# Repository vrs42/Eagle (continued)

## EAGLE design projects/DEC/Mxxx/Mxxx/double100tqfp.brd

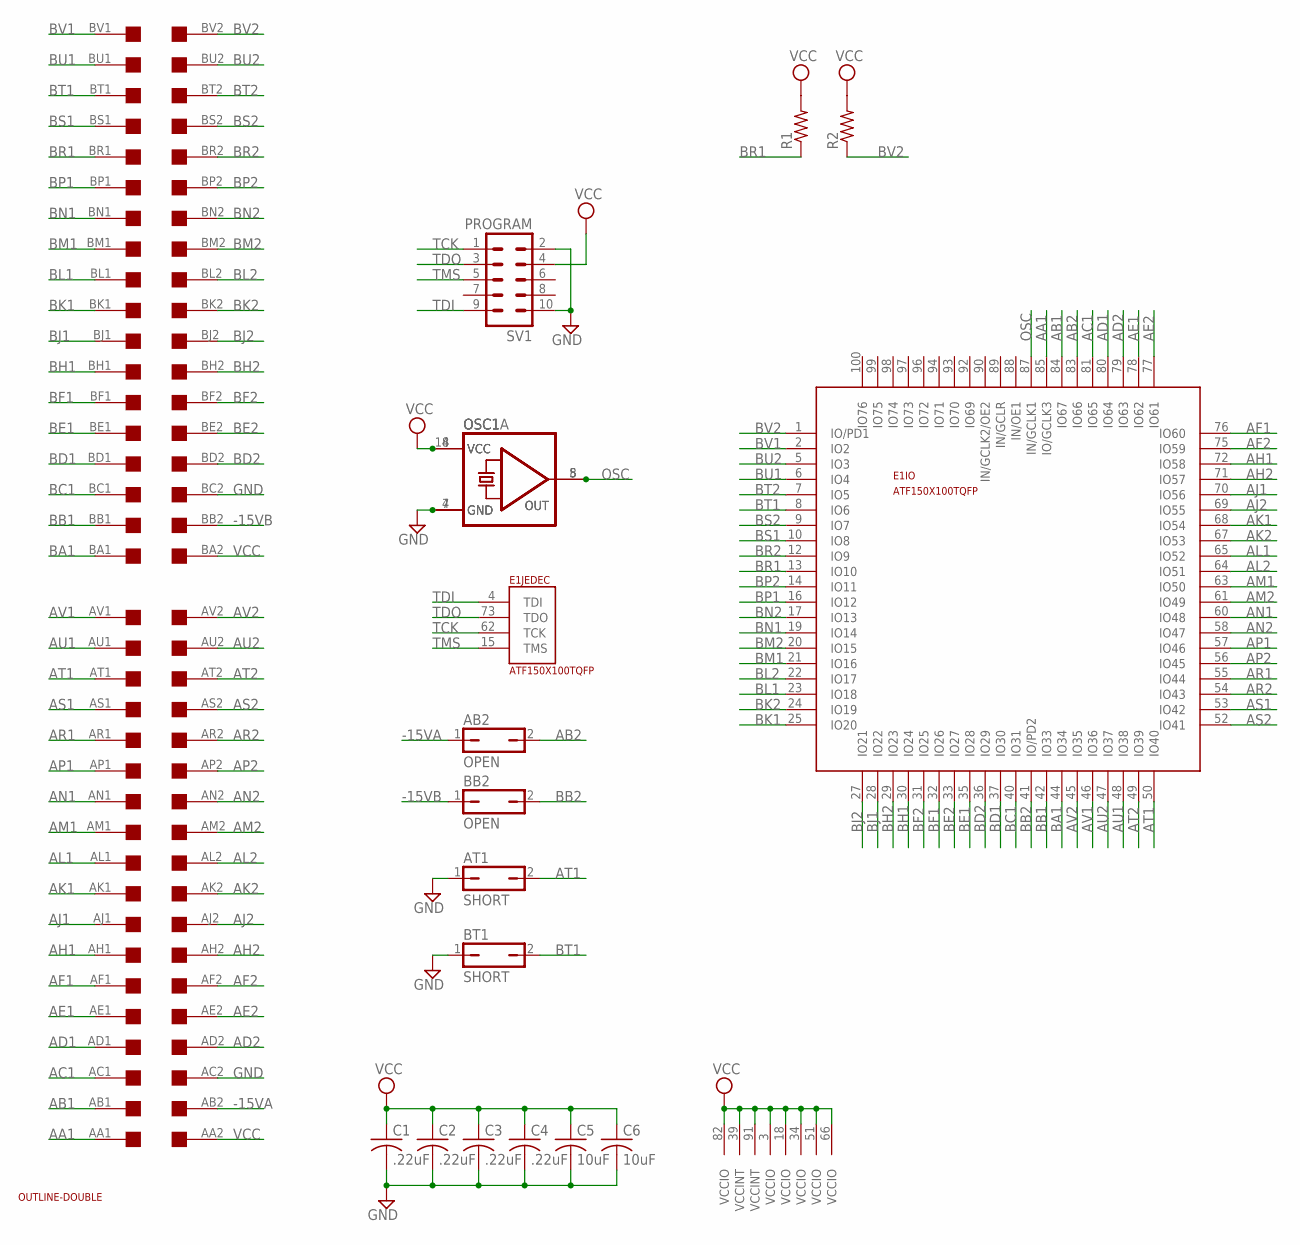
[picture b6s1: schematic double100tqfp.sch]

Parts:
AB2: OPEN; JP1
AT1: SHORT; JP1
BB2: OPEN; JP1
BT1: SHORT; JP1
C1, C2, C3, C4: .22uF; C0805
C5, C6: 10uF; C0805
E1: ATF150X100TQFP; TQFP-100
OSC1: DIL08S
OSC1A: DIL14S
R1, R2: 0207/10
SV1: PROGRAM; ML10
U$1: DOUBLE; EDGE-CON4
U$3: OUTLINE-DOUBLE; DOUBLE

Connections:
-15VA: AB2.1, U$1.AB2
-15VB: BB2.1, U$1.BB2
AA1: E1.85 (IO/GCLK3), U$1.AA1
AB1: E1.84 (IO67), U$1.AB1
AB2: AB2.2, E1.83 (IO66)
AC1: E1.81 (IO65), U$1.AC1
AD1: E1.80 (IO64), U$1.AD1
AD2: E1.79 (IO63), U$1.AD2
AE1: E1.78 (IO62), U$1.AE1
AE2: E1.77 (IO61), U$1.AE2
AF1: E1.76 (IO60), U$1.AF1
AF2: E1.75 (IO59), U$1.AF2
AH1: E1.72 (IO58), U$1.AH1
AH2: E1.71 (IO57), U$1.AH2
AJ1: E1.70 (IO56), U$1.AJ1
AJ2: E1.69 (IO55), U$1.AJ2
AK1: E1.68 (IO54), U$1.AK1
AK2: E1.67 (IO53), U$1.AK2
AL1: E1.65 (IO52), U$1.AL1
AL2: E1.64 (IO51), U$1.AL2
AM1: E1.63 (IO50), U$1.AM1
AM2: E1.61 (IO49), U$1.AM2
AN1: E1.60 (IO48), U$1.AN1
AN2: E1.58 (IO47), U$1.AN2
AP1: E1.57 (IO46), U$1.AP1
AP2: E1.56 (IO45), U$1.AP2
AR1: E1.55 (IO44), U$1.AR1
AR2: E1.54 (IO43), U$1.AR2
AS1: E1.53 (IO42), U$1.AS1
AS2: E1.52 (IO41), U$1.AS2
AT1: AT1.2, E1.50 (IO40), U$1.AT1
AT2: E1.49 (IO39), U$1.AT2
AU1: E1.48 (IO38), U$1.AU1
AU2: E1.47 (IO37), U$1.AU2
AV1: E1.46 (IO36), U$1.AV1
AV2: E1.45 (IO35), U$1.AV2
BA1: E1.44 (IO34), U$1.BA1
BB1: E1.42 (IO33), U$1.BB1
BB2: BB2.2, E1.41 (IO/PD2)
BC1: E1.40 (IO31), U$1.BC1
BD1: E1.37 (IO30), U$1.BD1
BD2: E1.36 (IO29), U$1.BD2
BE1: E1.35 (IO28), U$1.BE1
BE2: E1.33 (IO27), U$1.BE2
BF1: E1.32 (IO26), U$1.BF1
BF2: E1.31 (IO25), U$1.BF2
BH1: E1.30 (IO24), U$1.BH1
BH2: E1.29 (IO23), U$1.BH2
BJ1: E1.28 (IO22), U$1.BJ1
BJ2: E1.27 (IO21), U$1.BJ2
BK1: E1.25 (IO20), U$1.BK1
BK2: E1.24 (IO19), U$1.BK2
BL1: E1.23 (IO18), U$1.BL1
BL2: E1.22 (IO17), U$1.BL2
BM1: E1.21 (IO16), U$1.BM1
BM2: E1.20 (IO15), U$1.BM2
BN1: E1.19 (IO14), U$1.BN1
BN2: E1.17 (IO13), U$1.BN2
BP1: E1.16 (IO12), U$1.BP1
BP2: E1.14 (IO11), U$1.BP2
BR1: E1.13 (IO10), R1.1, U$1.BR1
BR2: E1.12 (IO9), U$1.BR2
BS1: E1.10 (IO8), U$1.BS1
BS2: E1.9 (IO7), U$1.BS2
BT1: BT1.2, E1.8 (IO6), U$1.BT1
BT2: E1.7 (IO5), U$1.BT2
BU1: E1.6 (IO4), U$1.BU1
BU2: E1.5 (IO3), U$1.BU2
BV1: E1.2 (IO2), U$1.BV1
BV2: E1.1 (IO/PD1), R2.1, U$1.BV2
GND: AT1.1, BT1.1, C1.2, C2.2, C3.2, C4.2, C5.2, C6.2, E1.11 (GND), E1.26 (GND), E1.38 (GND), E1.43 (GND), E1.59 (GND), E1.74 (GND), E1.86 (GND), E1.95 (GND), OSC1.4 (GND), OSC1A.7 (GND), SV1.2, SV1.10, U$1.AC2, U$1.BC2
OSC: E1.87 (IN/GCLK1), OSC1.5 (OUT), OSC1A.8 (OUT)
TCK: E1.62 (TCK), SV1.1
TDI: E1.4 (TDI), SV1.9
TDO: E1.73 (TDO), SV1.3
TMS: E1.15 (TMS), SV1.5
VCC: C1.1, C2.1, C3.1, C4.1, C5.1, C6.1, E1.3 (VCCIO), E1.18 (VCCIO), E1.34 (VCCIO), E1.39 (VCCINT), E1.51 (VCCIO), E1.66 (VCCIO), E1.82 (VCCIO), E1.91 (VCCINT), OSC1.8 (VCC), OSC1A.14 (VCC), R1.2, R2.2, SV1.4, U$1.AA2, U$1.BA2

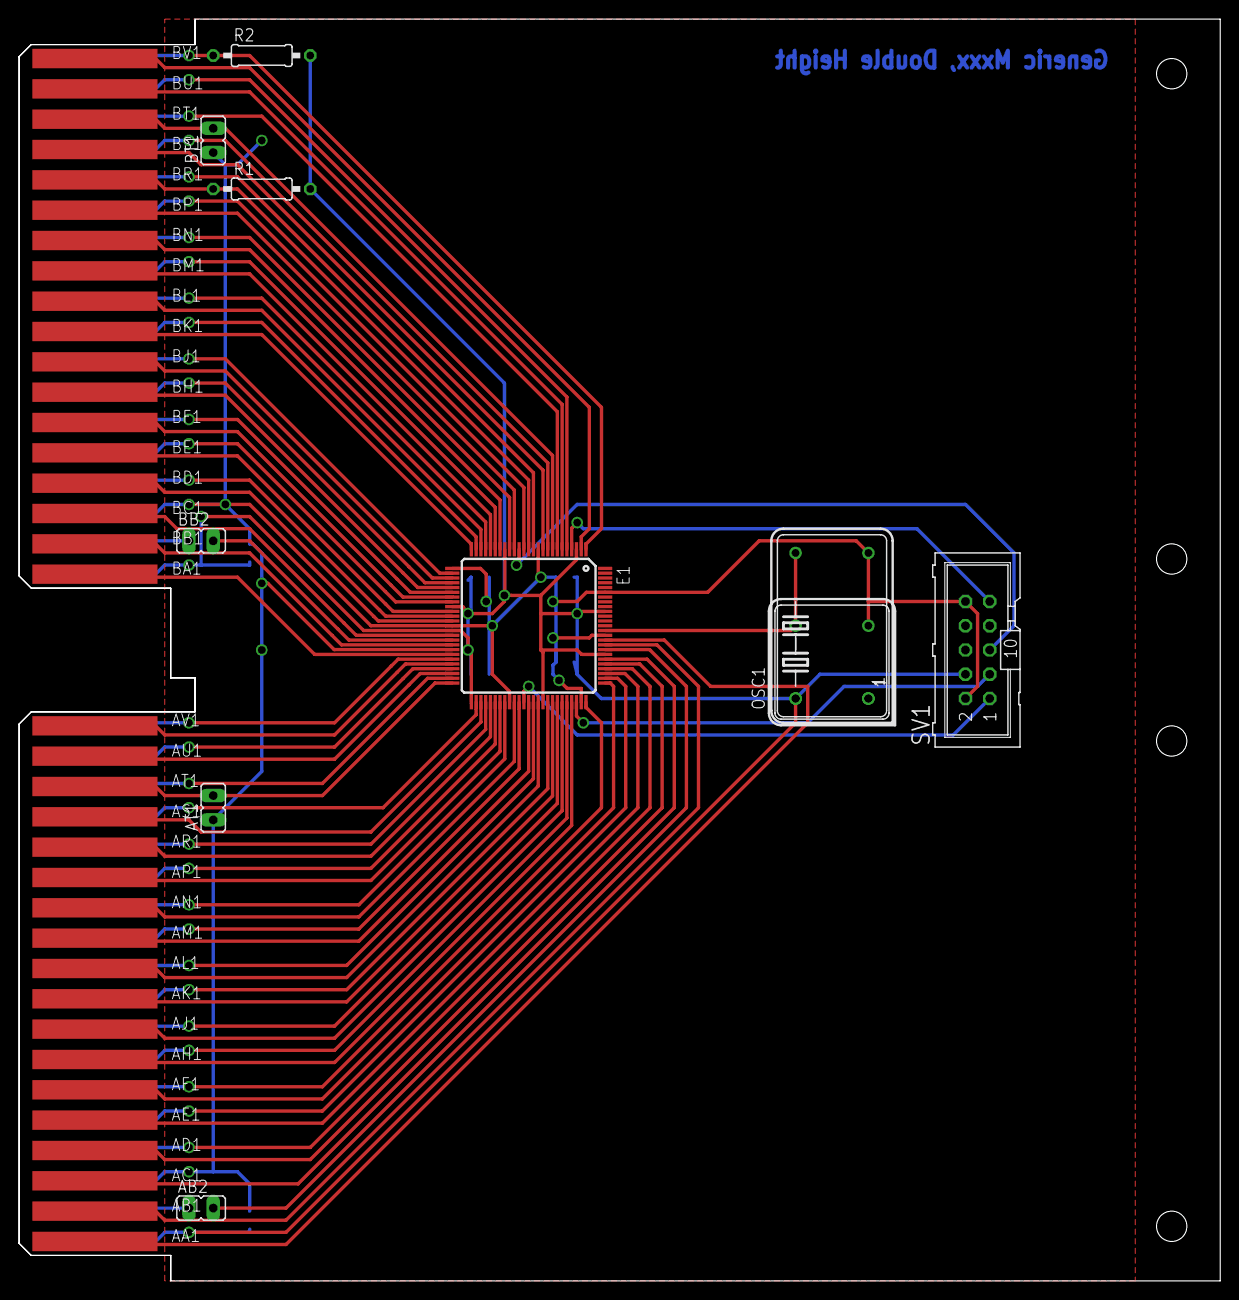
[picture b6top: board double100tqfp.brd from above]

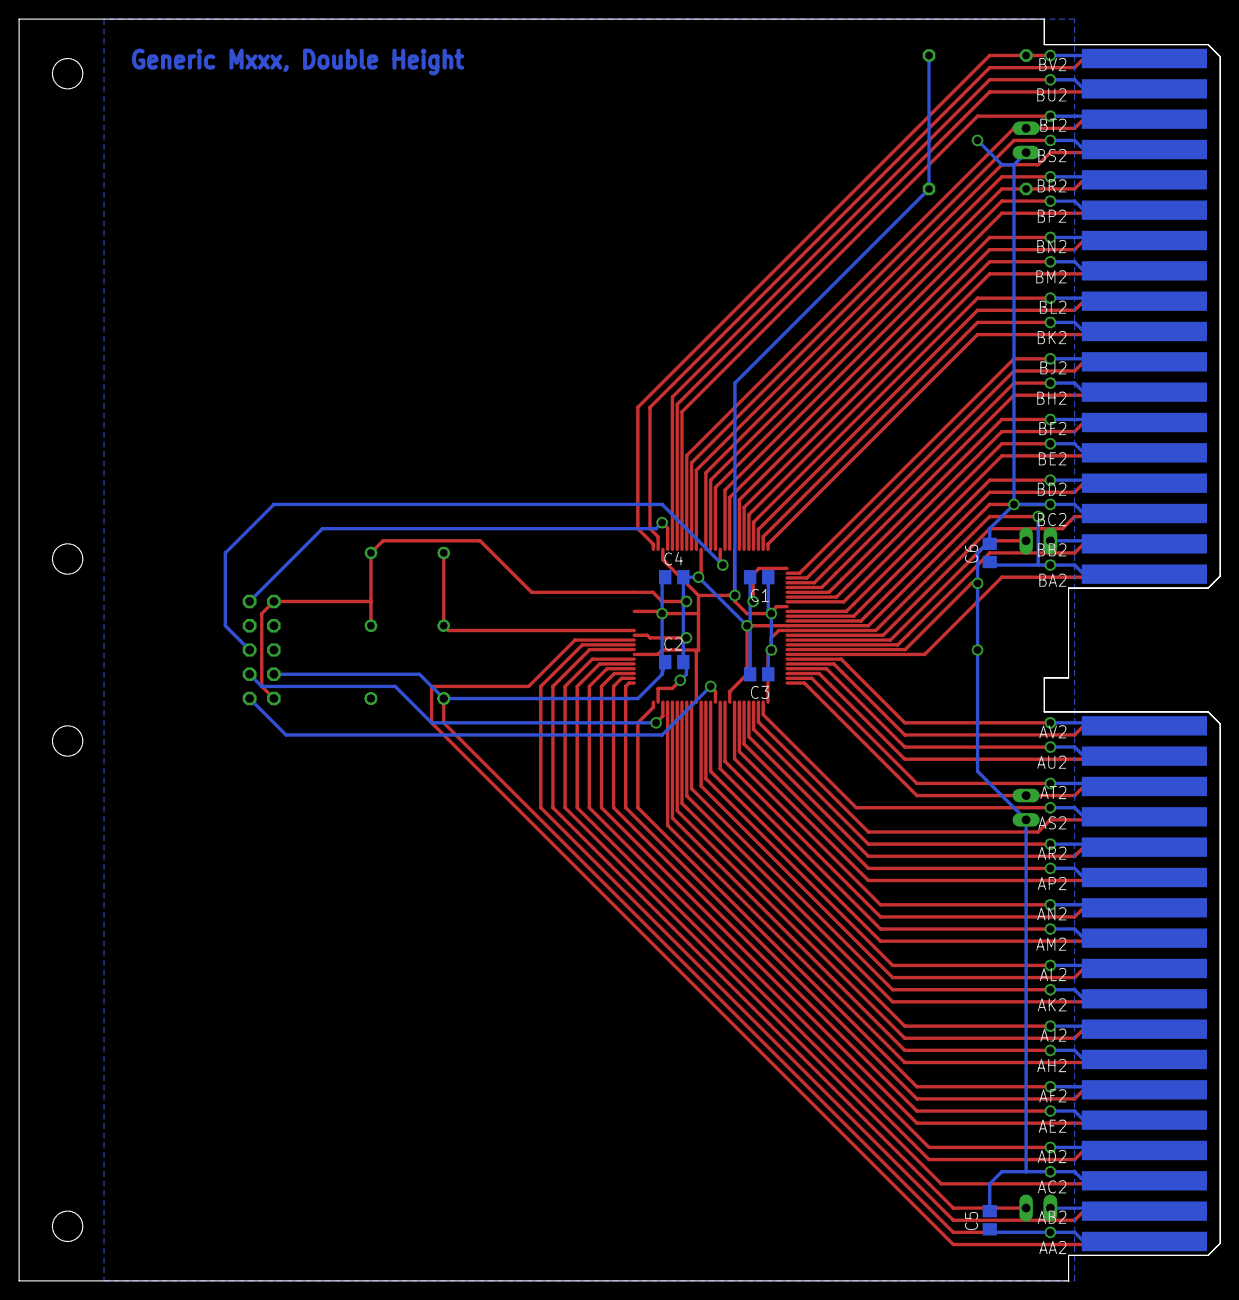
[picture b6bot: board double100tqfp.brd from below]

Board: 2 copper layers, 125.7 x 132.1 mm, 18 parts (6 on the bottom side), 77 nets.

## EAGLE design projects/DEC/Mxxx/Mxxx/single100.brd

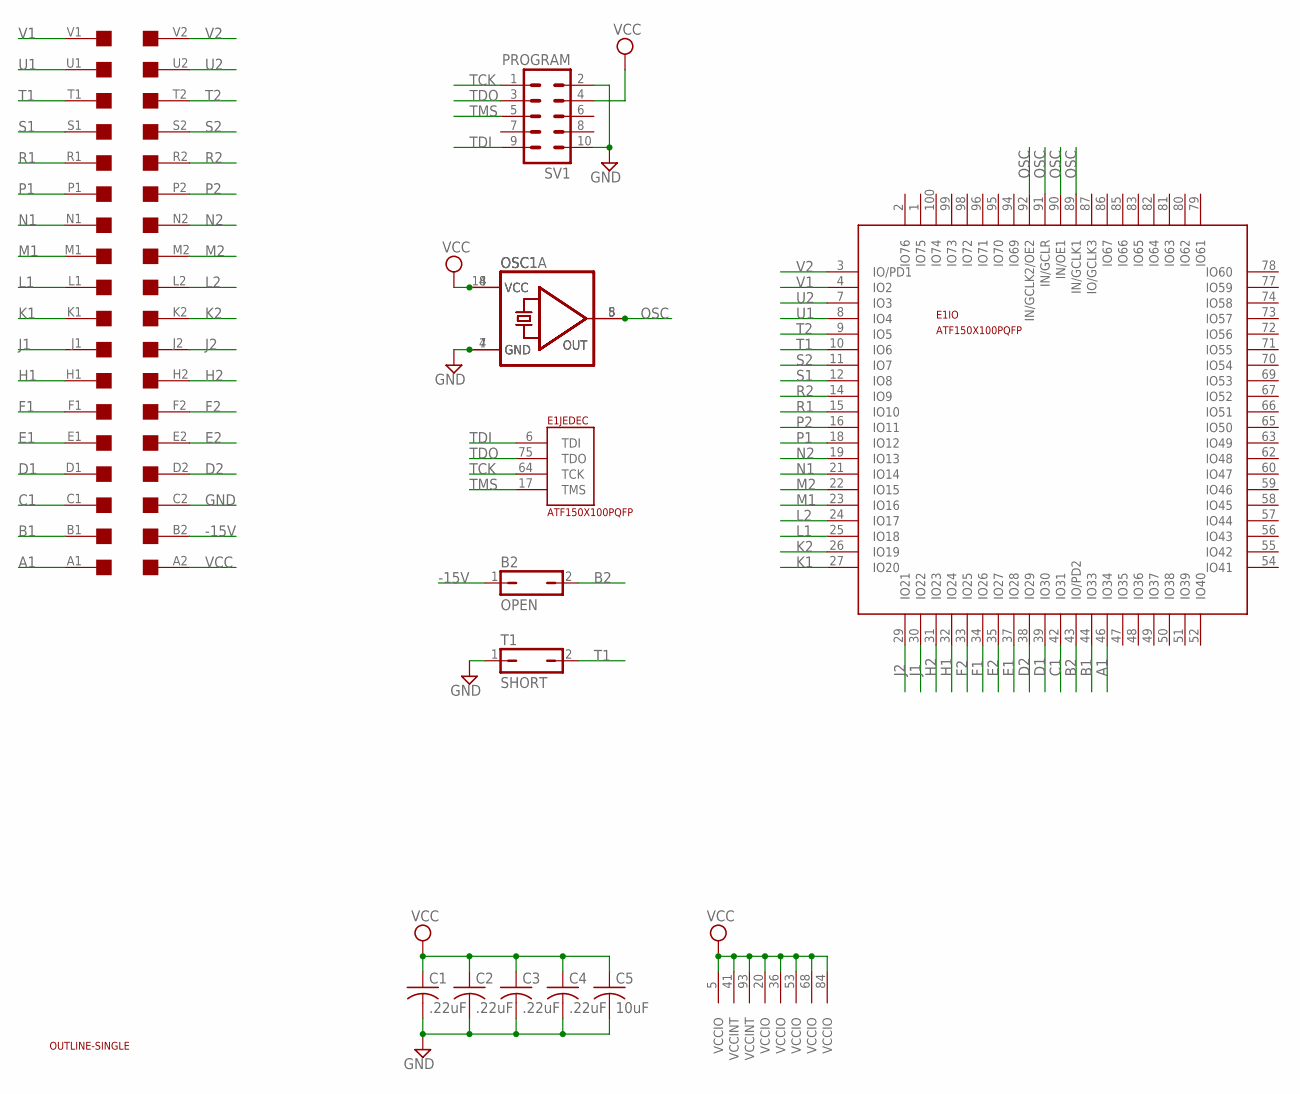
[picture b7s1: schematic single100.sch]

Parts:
B2: OPEN; JP1
C1, C2, C3, C4: .22uF; C0805
C5: 10uF; C0805
E1: ATF150X100PQFP; PQFP-100
OSC1: DIL08S
OSC1A: DIL14S
SV1: PROGRAM; ML10
T1: SHORT; JP1
U$1: OUTLINE-SINGLE; SINGLE
U$2: SINGLE; EDGE-CON2

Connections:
-15V: B2.1, U$2.B2
A1: E1.46 (IO34), U$2.A1
B1: E1.44 (IO33), U$2.B1
B2: B2.2, E1.43 (IO/PD2)
C1: E1.42 (IO31), U$2.C1
D1: E1.39 (IO30), U$2.D1
D2: E1.38 (IO29), U$2.D2
E1: E1.37 (IO28), U$2.E1
E2: E1.35 (IO27), U$2.E2
F1: E1.34 (IO26), U$2.F1
F2: E1.33 (IO25), U$2.F2
GND: C1.2, C2.2, C3.2, C4.2, C5.2, E1.13 (GND), E1.28 (GND), E1.40 (GND), E1.45 (GND), E1.61 (GND), E1.76 (GND), E1.88 (GND), E1.97 (GND), OSC1.4 (GND), OSC1A.7 (GND), SV1.2, SV1.10, T1.1, U$2.C2
H1: E1.32 (IO24), U$2.H1
H2: E1.31 (IO23), U$2.H2
J1: E1.30 (IO22), U$2.J1
J2: E1.29 (IO21), U$2.J2
K1: E1.27 (IO20), U$2.K1
K2: E1.26 (IO19), U$2.K2
L1: E1.25 (IO18), U$2.L1
L2: E1.24 (IO17), U$2.L2
M1: E1.23 (IO16), U$2.M1
M2: E1.22 (IO15), U$2.M2
N1: E1.21 (IO14), U$2.N1
N2: E1.19 (IO13), U$2.N2
OSC: E1.89 (IN/GCLK1), E1.90 (IN/OE1), E1.91 (IN/GCLR), E1.92 (IN/GCLK2/OE2), OSC1.5 (OUT), OSC1A.8 (OUT)
P1: E1.18 (IO12), U$2.P1
P2: E1.16 (IO11), U$2.P2
R1: E1.15 (IO10), U$2.R1
R2: E1.14 (IO9), U$2.R2
S1: E1.12 (IO8), U$2.S1
S2: E1.11 (IO7), U$2.S2
T1: E1.10 (IO6), T1.2, U$2.T1
T2: E1.9 (IO5), U$2.T2
TCK: E1.64 (TCK), SV1.1
TDI: E1.6 (TDI), SV1.9
TDO: E1.75 (TDO), SV1.3
TMS: E1.17 (TMS), SV1.5
U1: E1.8 (IO4), U$2.U1
U2: E1.7 (IO3), U$2.U2
V1: E1.4 (IO2), U$2.V1
V2: E1.3 (IO/PD1), U$2.V2
VCC: C1.1, C2.1, C3.1, C4.1, C5.1, E1.5 (VCCIO), E1.20 (VCCIO), E1.36 (VCCIO), E1.41 (VCCINT), E1.53 (VCCIO), E1.68 (VCCIO), E1.84 (VCCIO), E1.93 (VCCINT), OSC1.8 (VCC), OSC1A.14 (VCC), SV1.4, U$2.A2

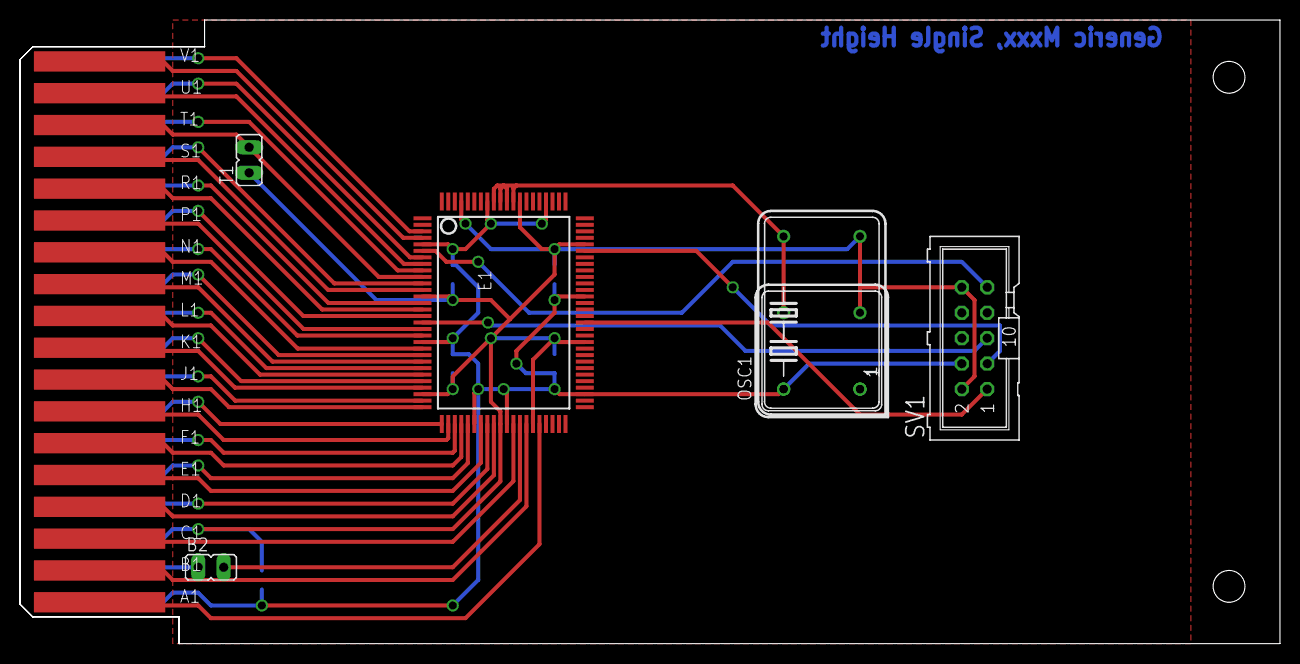
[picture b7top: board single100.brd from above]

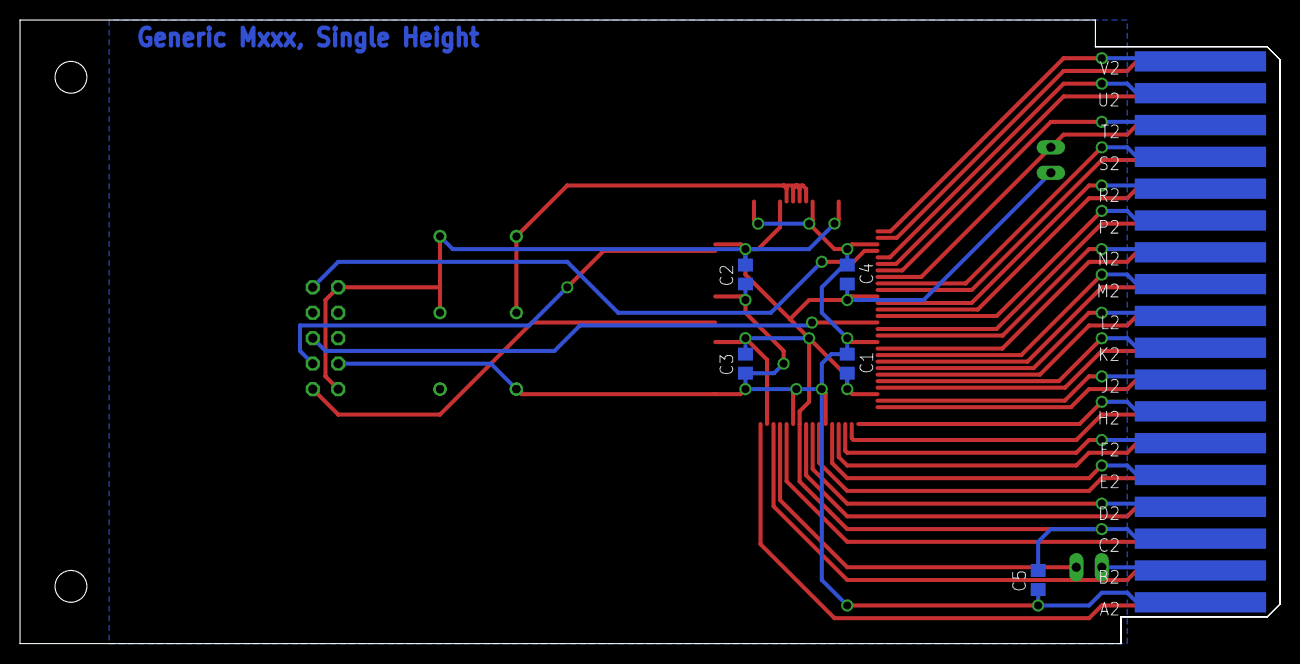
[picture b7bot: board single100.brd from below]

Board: 2 copper layers, 125.7 x 62.2 mm, 13 parts (5 on the bottom side), 42 nets.

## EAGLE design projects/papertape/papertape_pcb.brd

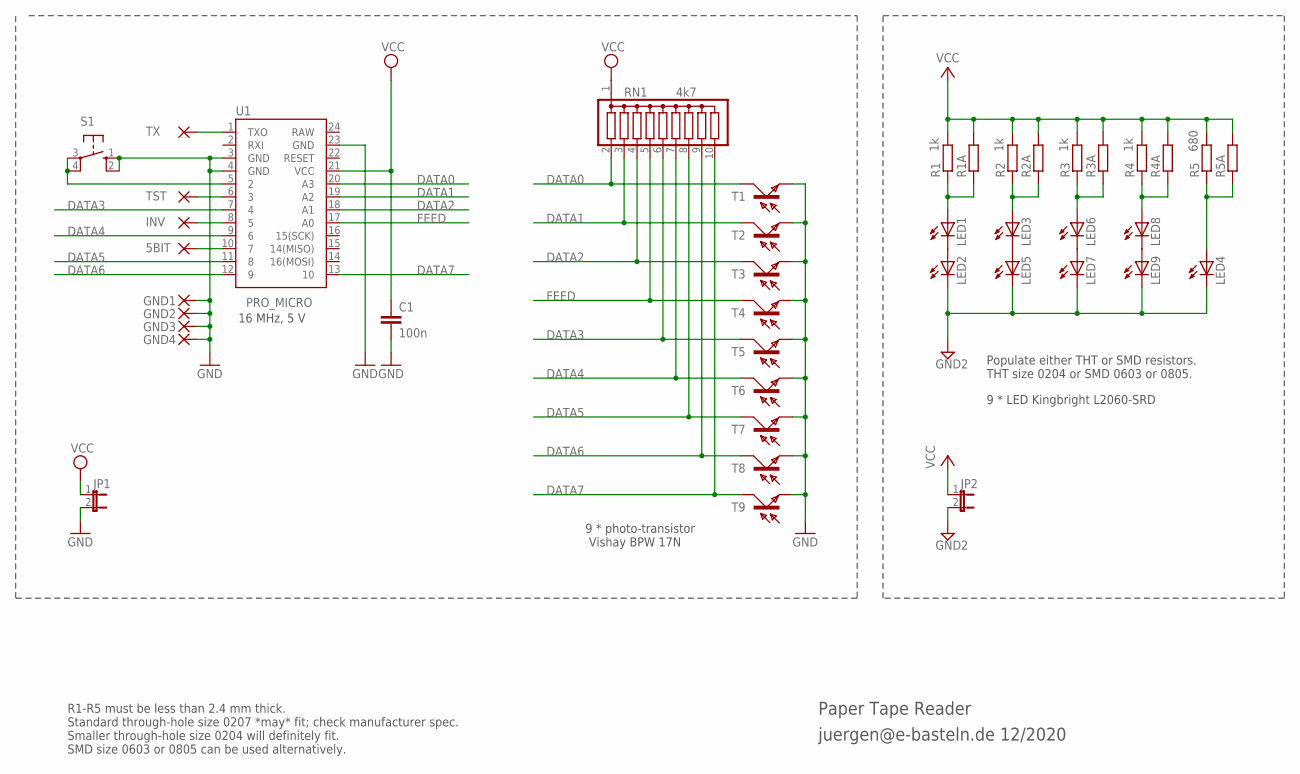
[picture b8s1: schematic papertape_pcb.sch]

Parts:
5BIT: 1,6/0,8
C1: 100n; C025-024X044
GND1, GND2, GND3, GND4: 1,6/0,8
INV: 1,6/0,8
JP1, JP2: JP1E; JP1
LED1, LED2, LED3, LED4, LED5, LED6, LED7, LED8, LED9: LEDLED1MM8; LED1MM8
R1, R2, R3, R4: 1k; 0204/7
R1A, R2A, R3A, R4A, R5A: R-EU_R0805; R0805
R5: 680; 0204/7
RN1: 4k7; SIL10
S1: 10-XX; B3F-10XX
T1, T2, T3, T4, T5, T6, T7, T8, T9: BPW17N
TST: 1,6/0,8
TX: 1,6/0,8
U1: PRO_MICRO; SPARKFUN_PRO_MICRO

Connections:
DATA0: RN1.2, T1.C, U1.20 (A3)
DATA1: RN1.3, T2.C, U1.19 (A2)
DATA2: RN1.4, T3.C, U1.18 (A1)
DATA3: RN1.6, T5.C, U1.7 (4)
DATA4: RN1.7, T6.C, U1.9 (6)
DATA5: RN1.8, T7.C, U1.11 (8)
DATA6: RN1.9, T8.C, U1.12 (9)
DATA7: RN1.10, T9.C, U1.13 (10)
FEED: RN1.5, T4.C, U1.17 (A0)
GND: C1.2, GND1.1, GND2.1, GND3.1, GND4.1, JP1.2, S1.1 (S), S1.2 (S1), T1.E, T2.E, T3.E, T4.E, T5.E, T6.E, T7.E, T8.E, T9.E, U1.3 (GND), U1.4 (GND), U1.23 (GND)
GND2: JP2.2, LED2.K (C), LED4.K (C), LED5.K (C), LED7.K (C), LED9.K (C)
unnamed: LED1.K (C), LED2.A
unnamed: LED3.K (C), LED5.A
unnamed: LED6.K (C), LED7.A
unnamed: LED8.K (C), LED9.A
unnamed: INV.1, U1.8 (5)
unnamed: TST.1, U1.6 (3)
unnamed: LED4.A, R5.1, R5A.1
unnamed: TX.1, U1.1 (TXO)
unnamed: 5BIT.1, U1.10 (7)
unnamed: S1.3, S1.4 (P1), U1.5 (2)
unnamed: LED1.A, R1.1, R1A.1
unnamed: LED3.A, R2.1, R2A.1
unnamed: LED6.A, R3.1, R3A.1
unnamed: LED8.A, R4.1, R4A.1
RAW: U1.24 (RAW)
VCC: C1.1, JP1.1, RN1.1, U1.21 (VCC)
VCC2: JP2.1, R1.2, R1A.2, R2.2, R2A.2, R3.2, R3A.2, R4.2, R4A.2, R5.2, R5A.2

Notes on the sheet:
16 MHz, 5 V
9 * photo-transistor Vishay BPW 17N
9 * LED Kingbright L2060-SRD
R1-R5 must be less than 2.4 mm thick. Standard through-hole size 0207 *may* fit; check manufacturer spec. Smaller through-hole size 0204 will definitely fit. SMD size 0603 or 0805 can be used alternatively.
Paper Tape Reader
juergen@e-basteln.de 12/2020
Populate either THT or SMD resistors. THT size 0204 or SMD 0603 or 0805.

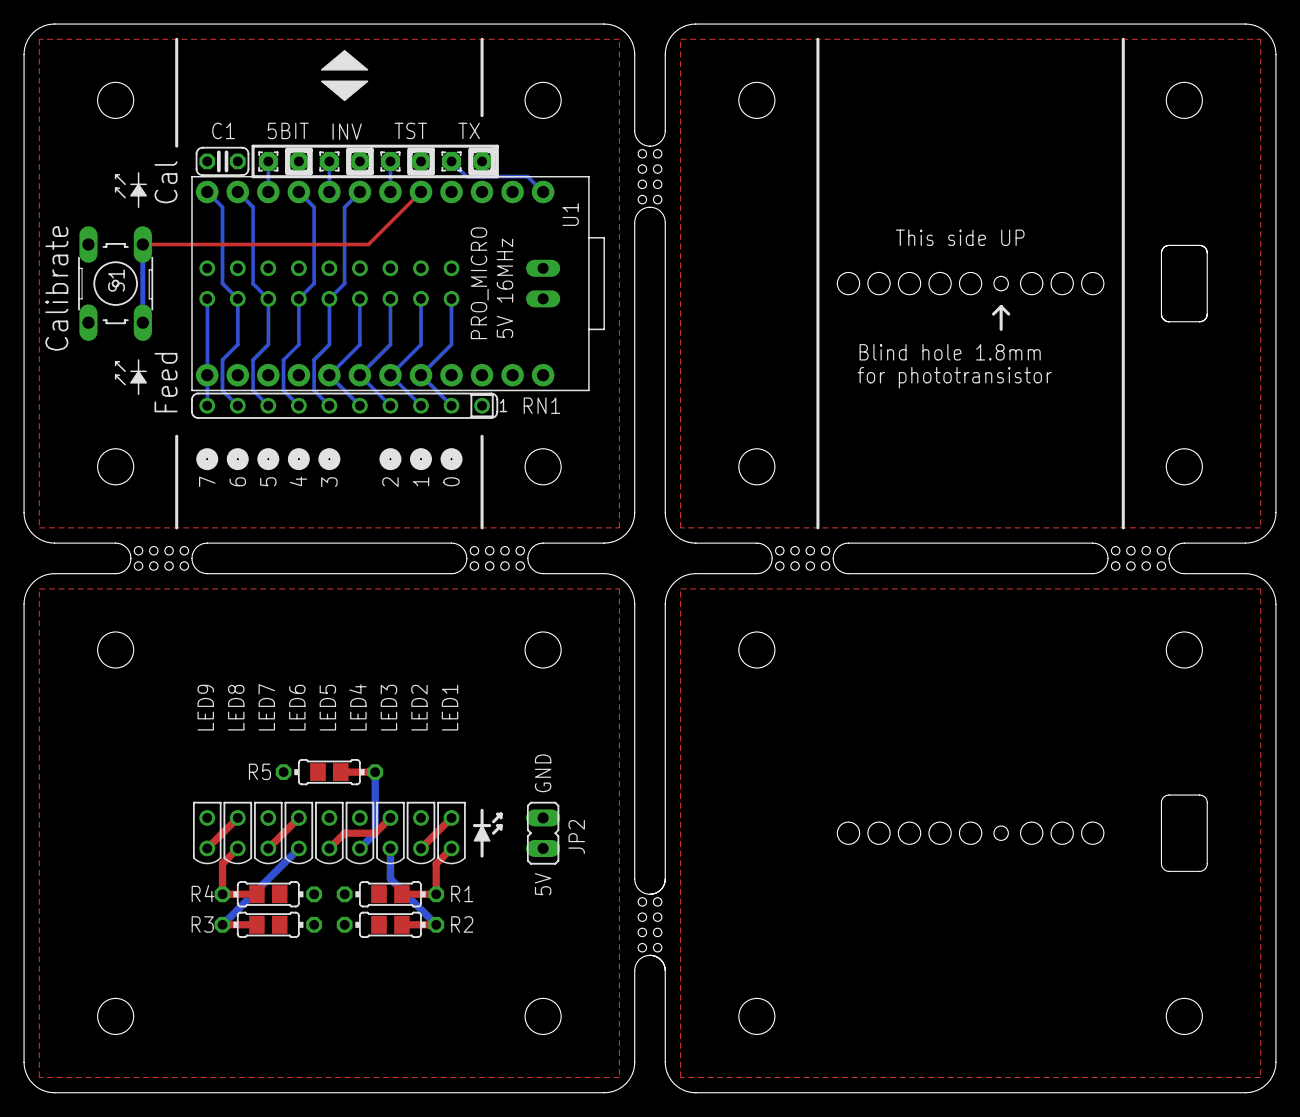
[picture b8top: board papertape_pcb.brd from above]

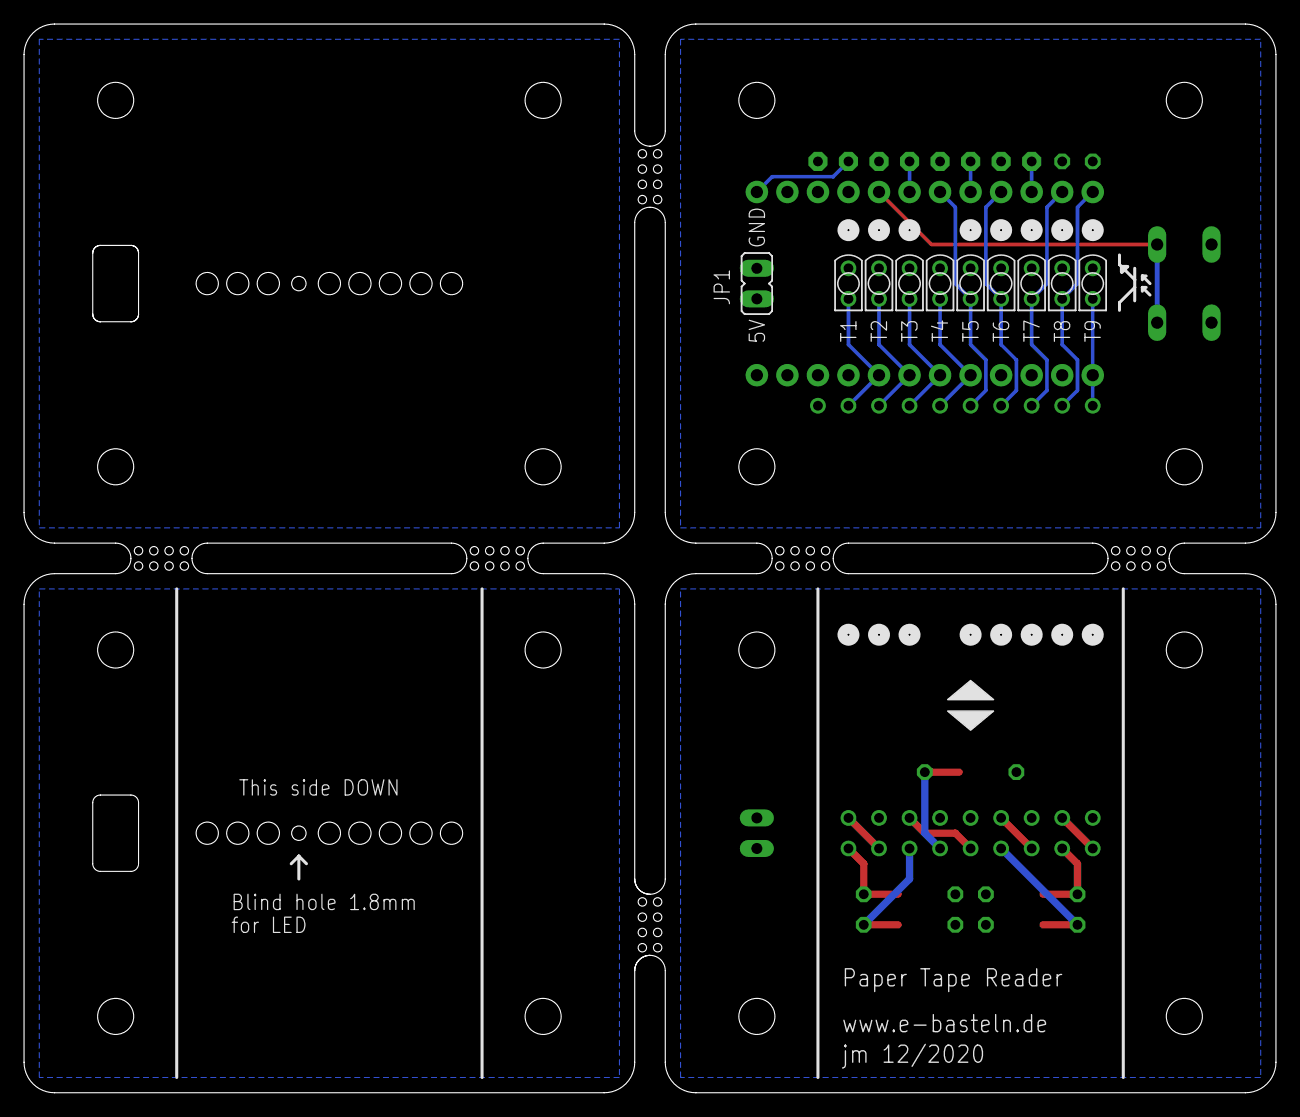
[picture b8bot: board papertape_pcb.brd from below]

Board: 2 copper layers, 104.1 x 88.9 mm, 42 parts (10 on the bottom side), 27 nets.

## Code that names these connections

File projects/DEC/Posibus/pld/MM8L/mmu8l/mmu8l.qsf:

# -------------------------------------------------------------------------- #
#
# Copyright (C) 1991-2013 Altera Corporation
# Your use of Altera Corporation's design tools, logic functions 
# and other software and tools, and its AMPP partner logic 
# functions, and any output files from any of the foregoing 
# (including device programming or simulation files), and any 
# associated documentation or information are expressly subject 
# to the terms and conditions of the Altera Program License 
# Subscription Agreement, Altera MegaCore Function License 
# Agreement, or other applicable license agreement, including, 
# without limitation, that your use is for the sole purpose of 
# programming logic devices manufactured by Altera and sold by 
# Altera or its authorized distributors.  Please refer to the 
# applicable agreement for further details.
#
# -------------------------------------------------------------------------- #
#
# Quartus II 64-Bit
# Version 13.0.1 Build 232 06/12/2013 Service Pack 1 SJ Web Edition
# Date created = 00:10:02  February 24, 2026
#
# -------------------------------------------------------------------------- #
#
# Notes:
#
# 1) The default values for assignments are stored in the file:
#		mmu8l_assignment_defaults.qdf
#    If this file doesn't exist, see file:
#		assignment_defaults.qdf
#
# 2) Altera recommends that you do not modify this file. This
#    file is updated automatically by the Quartus II software
#    and any changes you make may be lost or overwritten.
#
# -------------------------------------------------------------------------- #


set_global_assignment -name FAMILY MAX7000S
set_global_assignment -name DEVICE "EPM7128SQI100-10"
set_global_assignment -name TOP_LEVEL_ENTITY mmu8l
set_global_assignment -name ORIGINAL_QUARTUS_VERSION "13.0 SP1"
set_global_assignment -name PROJECT_CREATION_TIME_DATE "00:10:02  FEBRUARY 24, 2026"
set_global_assignment -name LAST_QUARTUS_VERSION "13.0 SP1"
set_global_assignment -name PROJECT_OUTPUT_DIRECTORY output_files
set_global_assignment -name ERROR_CHECK_FREQUENCY_DIVISOR "-1"
set_global_assignment -name TIMEQUEST_REPORT_SCRIPT_INCLUDE_DEFAULT_ANALYSIS OFF
set_global_assignment -name TIMEQUEST_DO_CCPP_REMOVAL OFF
set_global_assignment -name OPTIMIZE_HOLD_TIMING OFF
set_global_assignment -name OPTIMIZE_MULTI_CORNER_TIMING OFF
set_global_assignment -name FITTER_EFFORT "STANDARD FIT"
set_global_assignment -name VERILOG_FILE //wsl.localhost/Ubuntu/home/vrs/Verilog/projects/mmu8l/mc8l.v
set_global_assignment -name VERILOG_FILE //wsl.localhost/Ubuntu/home/vrs/Verilog/projects/mmu8l/mmu8l.v
set_global_assignment -name VERILOG_FILE //wsl.localhost/Ubuntu/home/vrs/Verilog/projects/mmu8l/mm32k.v
set_global_assignment -name MAX7000_DEVICE_IO_STANDARD TTL
set_global_assignment -name DEVICE_FILTER_PIN_COUNT 100
set_location_assignment PIN_3 -to AC_LOW
set_location_assignment PIN_78 -to ACLR_L
set_location_assignment PIN_4 -to KEY_DF_L[2]
set_location_assignment PIN_8 -to KEY_IF_L[2]
set_location_assignment PIN_7 -to POWER_OK
set_location_assignment PIN_9 -to STOP_OK
set_location_assignment PIN_16 -to BF_ENABLE_L
set_location_assignment PIN_42 -to DEL1
set_location_assignment PIN_43 -to DEL2
set_location_assignment PIN_44 -to DEL3
set_location_assignment PIN_46 -to DEL4
set_location_assignment PIN_47 -to DEL5
set_location_assignment PIN_48 -to DEL6
set_location_assignment PIN_22 -to DF_ENABLE_L
set_location_assignment PIN_30 -to EA[0]
set_location_assignment PIN_29 -to EA[1]
set_location_assignment PIN_27 -to EA[2]
set_location_assignment PIN_26 -to EA_L
set_location_assignment PIN_39 -to EMA
set_location_assignment PIN_38 -to EMA_L
set_location_assignment PIN_23 -to EXDA_L[0]
set_location_assignment PIN_24 -to EXDA_L[1]
set_location_assignment PIN_25 -to EXDA_L[2]
set_location_assignment PIN_21 -to E_OR_F_SET
set_location_assignment PIN_35 -to FIELD1
set_location_assignment PIN_66 -to IB_L[0]
set_location_assignment PIN_69 -to IB_L[1]
set_location_assignment PIN_71 -to IB_L[2]
set_location_assignment PIN_73 -to IB_L[3]
set_location_assignment PIN_77 -to IB_L[4]
set_location_assignment PIN_79 -to IB_L[5]
set_location_assignment PIN_81 -to IB_L[6]
set_location_assignment PIN_83 -to IB_L[7]
set_location_assignment PIN_86 -to IB_L[8]
set_location_assignment PIN_65 -to IB_L[9]
set_location_assignment PIN_67 -to IB_L[10]
set_location_assignment PIN_70 -to IB_L[11]
set_location_assignment PIN_91 -to INIT
set_location_assignment PIN_11 -to INT_INH_L
set_location_assignment PIN_92 -to IOP1
set_location_assignment PIN_87 -to IOP2
set_location_assignment PIN_89 -to IOP4
set_location_assignment PIN_74 -to IRQ_L
set_location_assignment PIN_18 -to JMP_OR_JMS
set_location_assignment PIN_12 -to KEY_CLR_L
set_location_assignment PIN_15 -to KEY_LOAD_L
set_location_assignment PIN_10 -to LOAD_SF_L
set_location_assignment PIN_49 -to MB[0]
set_location_assignment PIN_50 -to MB[1]
set_location_assignment PIN_51 -to MB[2]
set_location_assignment PIN_56 -to MB[3]
set_location_assignment PIN_59 -to MB[4]
set_location_assignment PIN_63 -to MB[5]
set_location_assignment PIN_52 -to MB[6]
set_location_assignment PIN_55 -to MB[7]
set_location_assignment PIN_57 -to MB[8]
set_location_assignment PIN_58 -to MB[9]
set_location_assignment PIN_60 -to MB[10]
set_location_assignment PIN_62 -to MB[11]
set_location_assignment PIN_34 -to MEMSTART
set_location_assignment PIN_72 -to SKIP_L
set_location_assignment PIN_19 -to SP_CYC_NEXT_L
set_location_assignment PIN_32 -to TP2
set_location_assignment PIN_14 -to TP3

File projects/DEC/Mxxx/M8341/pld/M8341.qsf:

# -------------------------------------------------------------------------- #
#
# Copyright (C) 1991-2013 Altera Corporation
# Your use of Altera Corporation's design tools, logic functions 
# and other software and tools, and its AMPP partner logic 
# functions, and any output files from any of the foregoing 
# (including device programming or simulation files), and any 
# associated documentation or information are expressly subject 
# to the terms and conditions of the Altera Program License 
# Subscription Agreement, Altera MegaCore Function License 
# Agreement, or other applicable license agreement, including, 
# without limitation, that your use is for the sole purpose of 
# programming logic devices manufactured by Altera and sold by 
# Altera or its authorized distributors.  Please refer to the 
# applicable agreement for further details.
#
# -------------------------------------------------------------------------- #
#
# Quartus II 64-Bit
# Version 13.0.1 Build 232 06/12/2013 Service Pack 1 SJ Web Edition
# Date created = 17:33:13  October 16, 2019
#
# -------------------------------------------------------------------------- #
#
# Notes:
#
# 1) The default values for assignments are stored in the file:
#		M8341_assignment_defaults.qdf
#    If this file doesn't exist, see file:
#		assignment_defaults.qdf
#
# 2) Altera recommends that you do not modify this file. This
#    file is updated automatically by the Quartus II software
#    and any changes you make may be lost or overwritten.
#
# -------------------------------------------------------------------------- #


set_global_assignment -name FAMILY MAX7000S
set_global_assignment -name DEVICE "EPM7128SQC100-15"
set_global_assignment -name TOP_LEVEL_ENTITY M8341
set_global_assignment -name ORIGINAL_QUARTUS_VERSION "13.0 SP1"
set_global_assignment -name PROJECT_CREATION_TIME_DATE "17:33:13  OCTOBER 16, 2019"
set_global_assignment -name LAST_QUARTUS_VERSION "13.0 SP1"
set_global_assignment -name VERILOG_FILE ../../M8340/pld/M8340.v
set_global_assignment -name PROJECT_OUTPUT_DIRECTORY output_files
set_global_assignment -name DEVICE_FILTER_PACKAGE PQFP
set_global_assignment -name DEVICE_FILTER_PIN_COUNT 100
set_global_assignment -name DEVICE_FILTER_SPEED_GRADE 15
set_global_assignment -name ERROR_CHECK_FREQUENCY_DIVISOR "-1"
set_global_assignment -name MIN_CORE_JUNCTION_TEMP 0
set_global_assignment -name MAX_CORE_JUNCTION_TEMP 85
set_location_assignment PIN_54 -to ac0
set_location_assignment PIN_57 -to ac0_ne_ac1
set_location_assignment PIN_51 -to ac1
set_location_assignment PIN_59 -to ac2_8_0
set_location_assignment PIN_42 -to ac4_11_0
set_location_assignment PIN_47 -to ac_0
set_location_assignment PIN_55 -to ad0_low
set_location_assignment PIN_48 -to carry_out_low
set_location_assignment PIN_92 -to clock
set_location_assignment PIN_83 -to dad_or_dst
set_location_assignment PIN_90 -to dad_or_dst_low
set_location_assignment PIN_77 -to div_12_l
set_location_assignment PIN_2 -to e
set_location_assignment PIN_71 -to eir2
set_location_assignment PIN_73 -to eir3
set_location_assignment PIN_3 -to fetch
set_location_assignment PIN_100 -to gtf_or_ind
set_location_assignment PIN_10 -to init
set_location_assignment PIN_95 -to last_step_l
set_location_assignment PIN_23 -to link
set_location_assignment PIN_99 -to modeb
set_location_assignment PIN_66 -to mq0_low
set_location_assignment PIN_67 -to mq10_low
set_location_assignment PIN_65 -to mq11_low
set_location_assignment PIN_56 -to mq_0
set_location_assignment PIN_4 -to msir_disable
set_location_assignment PIN_74 -to next_loc
set_location_assignment PIN_91 -to rom_11_l
set_location_assignment PIN_96 -to rom_12_l
set_location_assignment PIN_79 -to rom_13_l
set_location_assignment PIN_98 -to rom_14_l
set_location_assignment PIN_89 -to rom_15_l
set_location_assignment PIN_94 -to rom_17_l
set_location_assignment PIN_81 -to rom_22_l
set_location_assignment PIN_78 -to rom_24_l
set_location_assignment PIN_72 -to rtf
set_location_assignment PIN_70 -to sc_0_low
set_location_assignment PIN_86 -to sgt_low
set_location_assignment PIN_22 -to tp1
set_location_assignment PIN_19 -to tp2
set_location_assignment PIN_18 -to tp3
set_location_assignment PIN_16 -to ts2
set_location_assignment PIN_14 -to ts3
set_location_assignment PIN_11 -to ts4
set_location_assignment PIN_50 -to ac_load_low
set_location_assignment PIN_32 -to ac_to_bus_low
set_location_assignment PIN_49 -to ac_to_mq_ena_low
set_location_assignment PIN_52 -to ad_lk_low
set_location_assignment PIN_21 -to c0
set_location_assignment PIN_37 -to carry_in
set_location_assignment PIN_24 -to data1
set_location_assignment PIN_46 -to data_f
set_location_assignment PIN_31 -to data_t
set_location_assignment PIN_33 -to en0
set_location_assignment PIN_39 -to en1
set_location_assignment PIN_29 -to en2
set_location_assignment PIN_80 -to incr_sc
set_location_assignment PIN_60 -to left_low
set_location_assignment PIN_9 -to link_data
set_location_assignment PIN_7 -to link_load
set_location_assignment PIN_34 -to md_disable
set_location_assignment PIN_63 -to mq_data_low
set_location_assignment PIN_38 -to mq_load
set_location_assignment PIN_35 -to mq_to_bus_low
set_location_assignment PIN_15 -to not_last_xfer
set_location_assignment PIN_82 -to restart
set_location_assignment PIN_62 -to right_low
set_location_assignment PIN_30 -to shl_ena_low
set_location_assignment PIN_8 -to skip
set_location_assignment PIN_25 -to tp
set_location_assignment PIN_85 -to tp2_d

set_global_assignment -name MAX7000_DEVICE_IO_STANDARD TTL
